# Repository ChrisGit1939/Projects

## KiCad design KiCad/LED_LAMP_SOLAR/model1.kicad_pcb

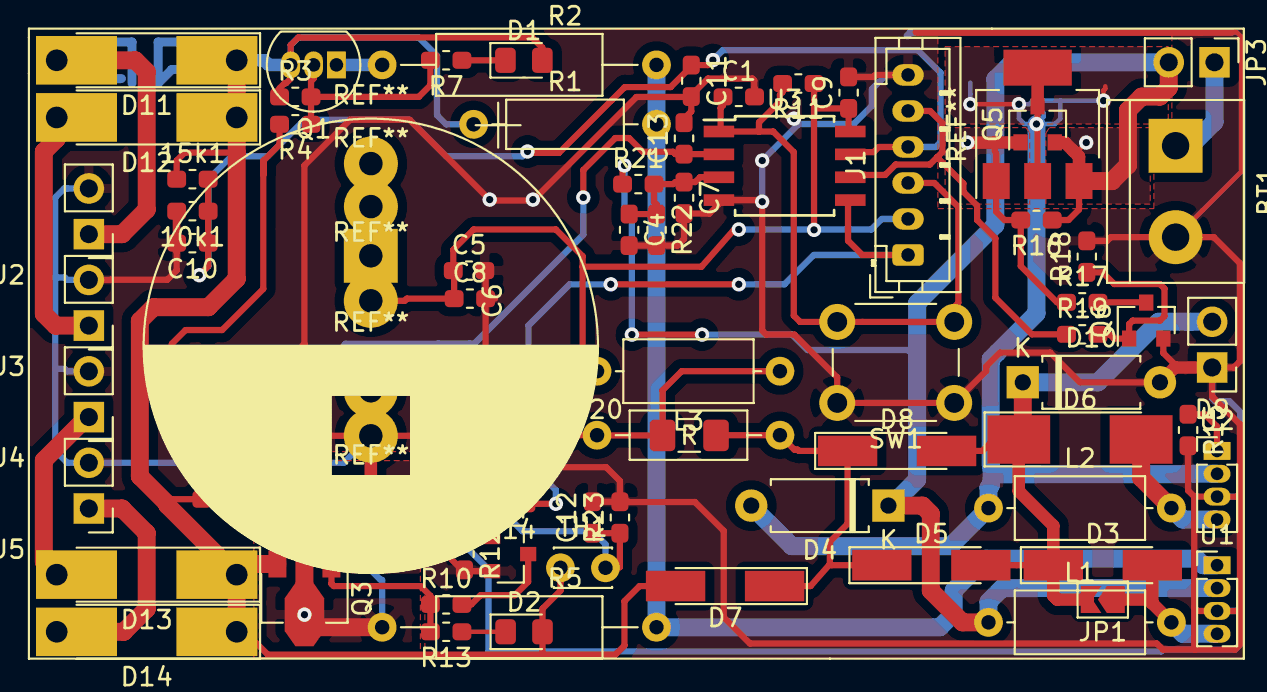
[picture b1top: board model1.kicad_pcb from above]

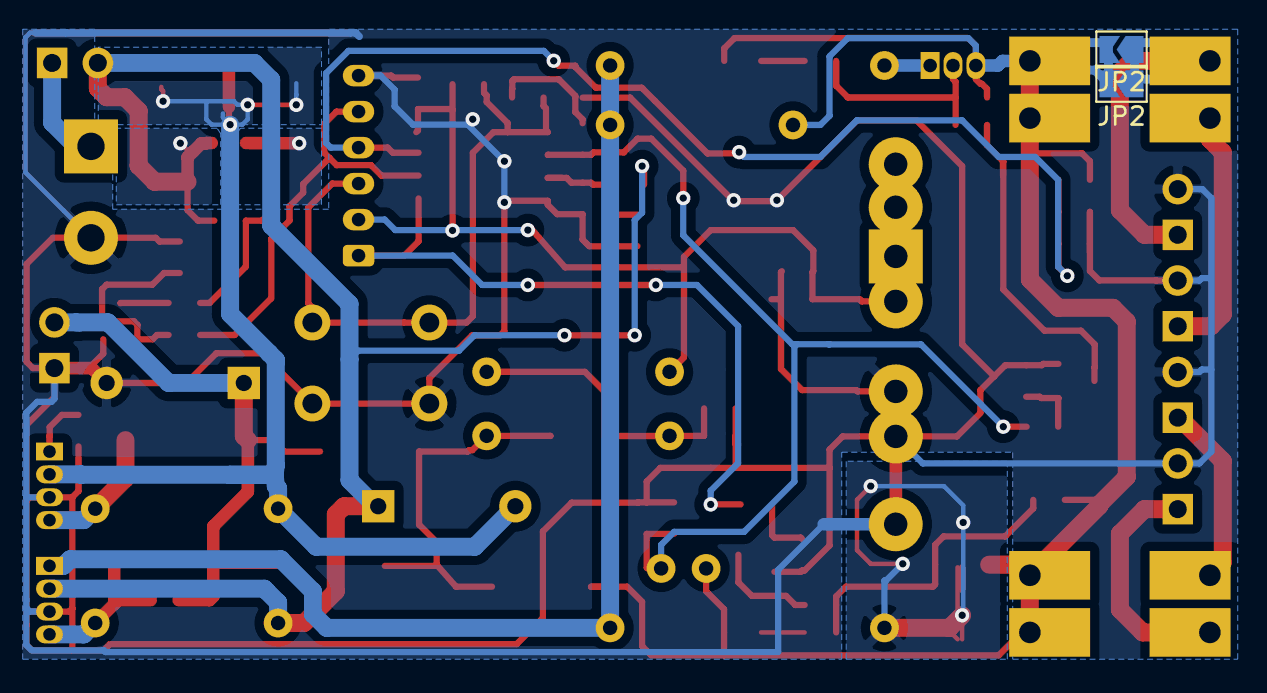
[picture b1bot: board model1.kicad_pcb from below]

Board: 2 copper layers, 77 parts (2 on the bottom side), 36 nets.

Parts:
10k1, 15k1: R; R_0603_1608Metric_Pad1.05x0.95mm_HandSolder
BT1: Battery_Cell; TerminalBlock_bornier-2_P5.08mm
C1, C2, C3, C4, C5, C7, C8, C9, C10, C11: 100n; C_0603_1608Metric_Pad1.05x0.95mm_HandSolder
C6: 1F/5V5; CP_Radial_D25.0mm_P10.00mm_SnapIn
C12, C13: C; C_0603_1608Metric_Pad1.05x0.95mm_HandSolder
D1, D2: LED; LED_0805_2012Metric_Pad1.15x1.40mm_HandSolder
D3, D5, D7, D8: D_Schottky; D_MiniMELF_Handsoldering
D4: D; D_A-405_P7.62mm_Horizontal
D6: D_Schottky; D_MELF_Handsoldering
D9: LED; PinHeader_1x02_P2.54mm_Vertical
D10: 7,5V; D_A-405_P7.62mm_Horizontal
D11, D12, D13, D14: D_Schottky; D_MELF-RM10_Universal_Handsoldering
J1: Conn_01x06_Male; JST_PH_B6B-PH-K_1x06_P2.00mm_Vertical
J2, J3, J4, J5: Solar; PinHeader_1x02_P2.54mm_Vertical
JP1, JP2, JP2#2: Jumper; SolderJumper-2_P1.3mm_Open_TrianglePad1.0x1.5mm
JP3: Jumper; PinHeader_1x02_P2.54mm_Vertical
L1: 330uH; L_Axial_L7.0mm_D3.3mm_P10.16mm_Horizontal_Fastron_MICC
L2: 4,7uH; L_Axial_L7.0mm_D3.3mm_P10.16mm_Horizontal_Fastron_MICC
L3: 10uH; L_Axial_L7.0mm_D3.3mm_P10.16mm_Horizontal_Fastron_MICC
Q1: BC327; TO-92_Inline
Q2, Q4, Q6: BC817; SOT-23
Q3: BCX51; SOT-89-3
Q5: SI2301; SOT-23
R: R_1206_3216Metric_Pad1.42x1.75mm_HandSolder
R1, R20: 47R; R_Axial_DIN0207_L6.3mm_D2.5mm_P10.16mm_Horizontal
R2: 3R3; R_Axial_DIN0309_L9.0mm_D3.2mm_P15.24mm_Horizontal
R3, R6, R9, R12, R16, R18: 180k; R_0603_1608Metric_Pad1.05x0.95mm_HandSolder
R4, R10, R15, R17: 1k; R_0603_1608Metric_Pad1.05x0.95mm_HandSolder
R5: R100; R_Axial_DIN0309_L9.0mm_D3.2mm_P15.24mm_Horizontal
R7, R13: 3k6; R_0603_1608Metric_Pad1.05x0.95mm_HandSolder
R8, R14, R19, R22: 15k; R_0603_1608Metric_Pad1.05x0.95mm_HandSolder
R11: 10k; R_0603_1608Metric_Pad1.05x0.95mm_HandSolder
R21: 6k2; R_0603_1608Metric_Pad1.05x0.95mm_HandSolder
R23: R; R_0603_1608Metric_Pad1.05x0.95mm_HandSolder
SW1: SW_Push; SW_PUSH_6mm
TH1: Thermistor_NTC; C_Disc_D3.0mm_W2.0mm_P2.50mm
U1, U2: QX5252; PinHeader_1x04_P1.27mm_Vertical
U3: ATtiny13A-SU; SOIJ-8_5.3x5.3mm_P1.27mm

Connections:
+1V2: D4.1, JP3.2, L1.1, Q5.2, R16.1, R21.1, U1.2
+2V5: 15k1.1, D1.2, D2.2, D7.2, D11.1, D12.1, D13.1, D14.1, JP2.2, JP2#2.2, Q1.3, Q3.3, R1.1, R3.1, R9.1, TH1.1
GND: 10k1.2, BT1.2, C1.2, C2.2, C3.2, C4.2, C5.2, C6.2, C7.2, C8.2, C9.2, C10.2, C11.2, C12.2, C13.2, D9.1, D10.2, J1.6, J2.2, J3.2, J4.2, J5.2, Q2.2, Q4.2, Q6.2, R6.2, R12.2, R15.2, R18.2, R22.2, R23.2, SW1.1, U1.3, U2.3, U3.4
LED: D3.1, D5.2, D6.1, D8.2, D9.2, D10.1, JP1.2
MISO: J1.5, R19.1, U3.6
MOSI: J1.1, R14.1, U3.5
unnamed: BT1.1, JP3.1
unnamed: C2.1, C3.1, L3.1, R.1, R20.1
unnamed: C4.1, C7.1, R21.2, R22.1, U3.3
unnamed: C12.1, C13.1, R8.1, R23.1, TH1.2, U3.2
unnamed: D1.1, R7.1
unnamed: D2.1, R13.1
unnamed: D3.2, JP1.1, L1.2, U1.4
unnamed: D4.2, L2.1, Q5.3, U2.2
unnamed: D5.1, D7.1, D8.1, R.2, R20.2
unnamed: D6.2, L2.2, U2.4
unnamed: D11.2, J2.1, JP2.1, JP2#2.1
unnamed: D12.2, J3.1
unnamed: D13.2, J4.1
unnamed: D14.2, J5.1
unnamed: Q1.1, R2.1
unnamed: Q1.2, R3.2, R4.1, R7.2
unnamed: Q2.1, R6.1, R8.2
unnamed: Q2.3, R4.2
unnamed: Q3.1, R9.2, R10.1, R13.2
unnamed: Q3.2, R5.1
unnamed: Q4.1, R12.1, R14.2
unnamed: Q4.3, R10.2
unnamed: Q5.1, R16.2, R17.1
unnamed: Q6.1, R18.1, R19.2
unnamed: Q6.3, R17.2
unnamed: R1.2, R2.2, R5.2, U1.1
unnamed: R15.1, U2.1
RST: C1.1, J1.3, R11.2, SW1.2, U3.1
SCK: 10k1.1, 15k1.2, C10.1, C11.1, J1.4, U3.7
VCC: C5.1, C6.1, C8.1, C9.1, J1.2, L3.2, R11.1, U3.8

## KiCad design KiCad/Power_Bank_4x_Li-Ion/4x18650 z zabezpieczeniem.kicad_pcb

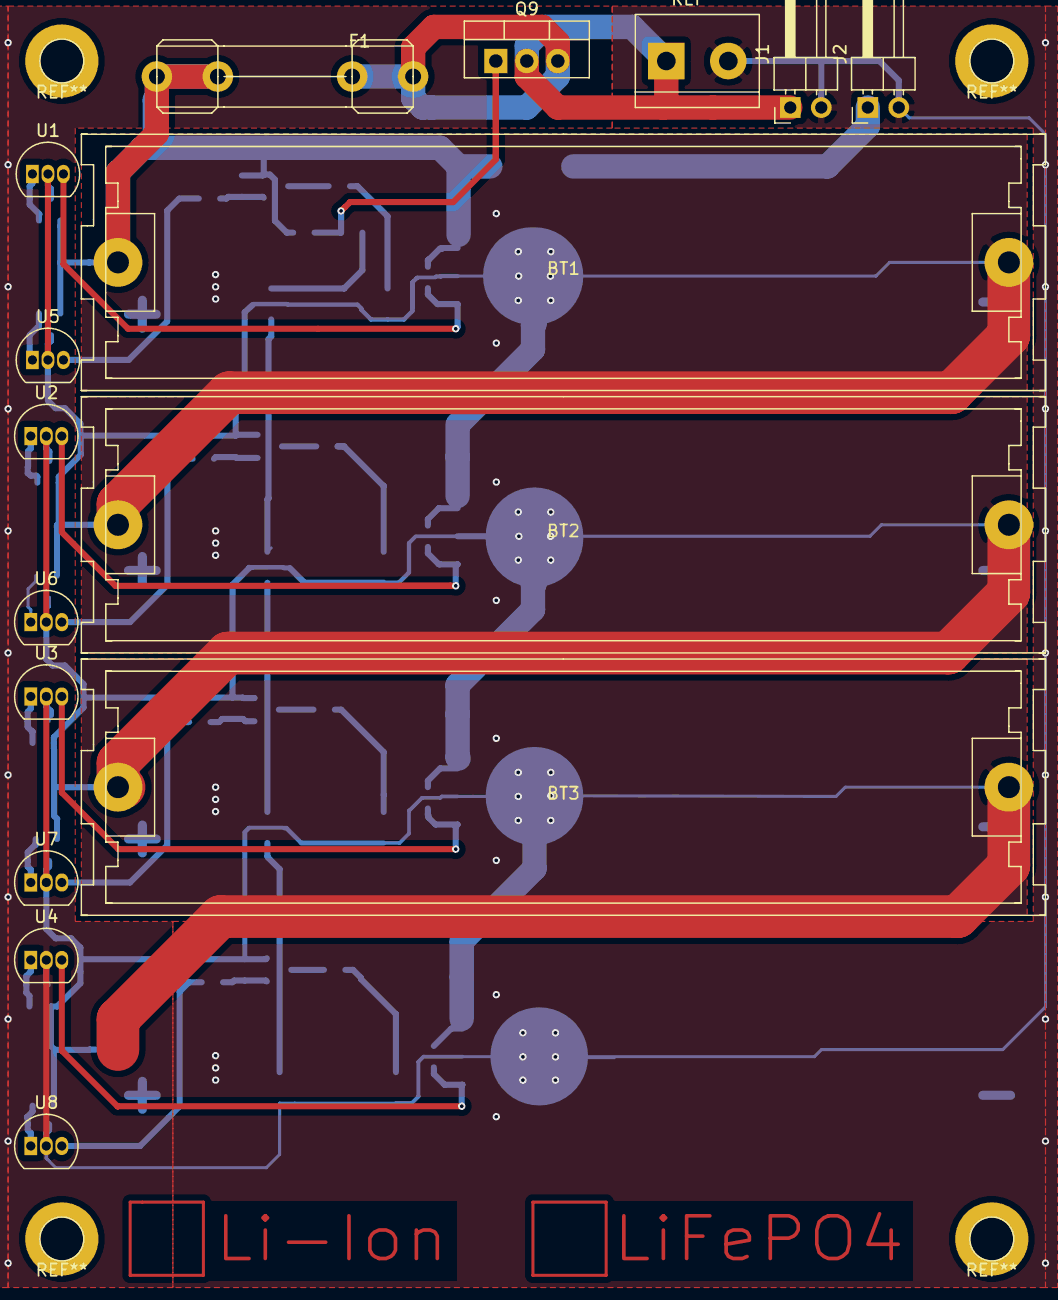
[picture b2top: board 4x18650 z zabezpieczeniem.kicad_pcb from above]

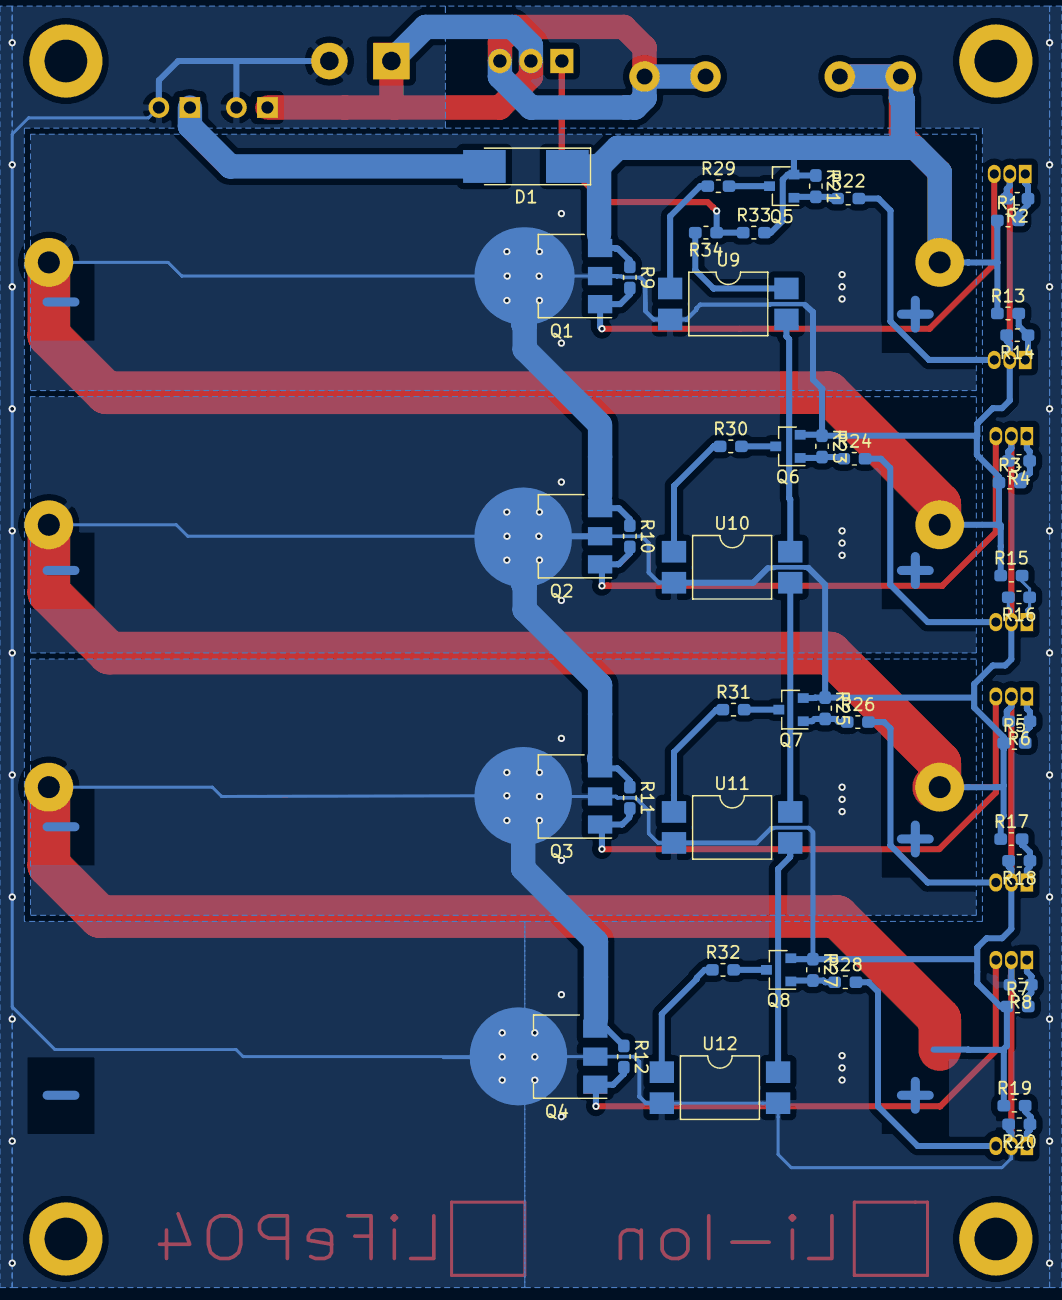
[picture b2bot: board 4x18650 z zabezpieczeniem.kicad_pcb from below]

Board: 2 copper layers, 62 parts (47 on the bottom side), 41 nets.

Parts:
BT1, BT2, BT3: Battery_Cell; BatteryHolder_18650_2
D1: D; D_MELF_Handsoldering
F1: Fuse; FuseHolder_5x20
J1, J2: Conn_01x02_Female; PinHeader_1x02_P2.54mm_Horizontal
Q1, Q2, Q3, Q4: BCP53; SOT-223-3_TabPin2
Q5, Q6, Q7, Q8: BC807; SOT-23
Q9: Q_PMOS_GDS; TO-220-3_Vertical
R1, R2, R3, R4, R5, R6, R7, R8, R9, R10, R11, R12, R13, R14, R15, R16, R17, R18, R19, R20, R29, R30, R31, R32, R33, R34: R; R_0603_1608Metric_Pad1.05x0.95mm_HandSolder
R21, R22, R23, R24, R25, R26, R27, R28: R_Small; R_0603_1608Metric_Pad1.05x0.95mm_HandSolder
U1, U2, U3, U4, U5, U6, U7, U8: TL431LP; TO-92_Inline
U9, U10, U11, U12: LTV-817S; SMDIP-4_W9.53mm

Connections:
GND: J1.2, J2.2, Q4.2, R8.2, R20.2, U4.2, U8.2, U12.2, U12.3
unnamed: BT1.2, BT2.1, Q1.2, Q2.3, Q6.2, R2.2, R3.1, R10.1, R14.2, R15.1, R23.1, U1.2, U5.2, U9.2
unnamed: BT2.2, BT3.1, Q2.2, Q3.3, Q7.2, R4.2, R5.1, R11.1, R16.2, R17.1, R25.1, U2.2, U6.2, U10.2
unnamed: BT3.2, Q3.2, Q4.3, Q8.2, R6.2, R7.1, R12.1, R18.2, R19.1, R27.1, U3.2, U7.2, U11.2
unnamed: D1.2, J2.1
unnamed: F1.2, Q9.3
unnamed: J1.1, Q9.2
unnamed: Q1.1, R9.2, U1.3
unnamed: Q2.1, R10.2, U2.3
unnamed: Q3.1, R11.2, U3.3
unnamed: Q4.1, R12.2, U4.3
unnamed: Q5.1, R21.2, R22.1
unnamed: Q5.3, R29.2
unnamed: Q6.1, R23.2, R24.1
unnamed: Q6.3, R30.2
unnamed: Q7.1, R25.2, R26.1
unnamed: Q7.3, R31.2
unnamed: Q8.1, R27.2, R28.1
unnamed: Q8.3, R32.2
unnamed: Q9.1, R33.1, R34.1
unnamed: R1.2, R2.1, U1.1
unnamed: R3.2, R4.1, U2.1
unnamed: R5.2, R6.1, U3.1
unnamed: R7.2, R8.1, U4.1
unnamed: R13.2, R14.1, U5.1
unnamed: R15.2, R16.1, U6.1
unnamed: R17.2, R18.1, U7.1
unnamed: R19.2, R20.1, U8.1
unnamed: R22.2, U5.3
unnamed: R24.2, U6.3
unnamed: R26.2, U7.3
unnamed: R28.2, U8.3
unnamed: R29.1, U9.1
unnamed: R30.1, U10.1
unnamed: R31.1, U11.1
unnamed: R32.1, U12.1
unnamed: R34.2, U9.4
unnamed: U10.3, U11.4
unnamed: U9.3, U10.4
unnamed: U11.3, U12.4
VCC: BT1.1, D1.1, F1.1, Q1.3, Q5.2, R1.1, R9.1, R13.1, R21.1, R33.2

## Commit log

2022-05-22 Dodanie pliku z kodem źródłowym
2022-05-23 Wyłącznik zmierzchowy na bazie mikrokontrolera Attiny13
2022-05-23 Projekt zegarka na ATmega8 sterowanie enkoderem z LCD PCD8544
2022-06-05 Add new project
2022-06-10 Add new program
2022-06-10 Add new project: Weather Indicator version in terminal
2022-06-14 New projects
